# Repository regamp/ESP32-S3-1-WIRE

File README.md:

ESP32_S3 Waveshare IO and 1-wire

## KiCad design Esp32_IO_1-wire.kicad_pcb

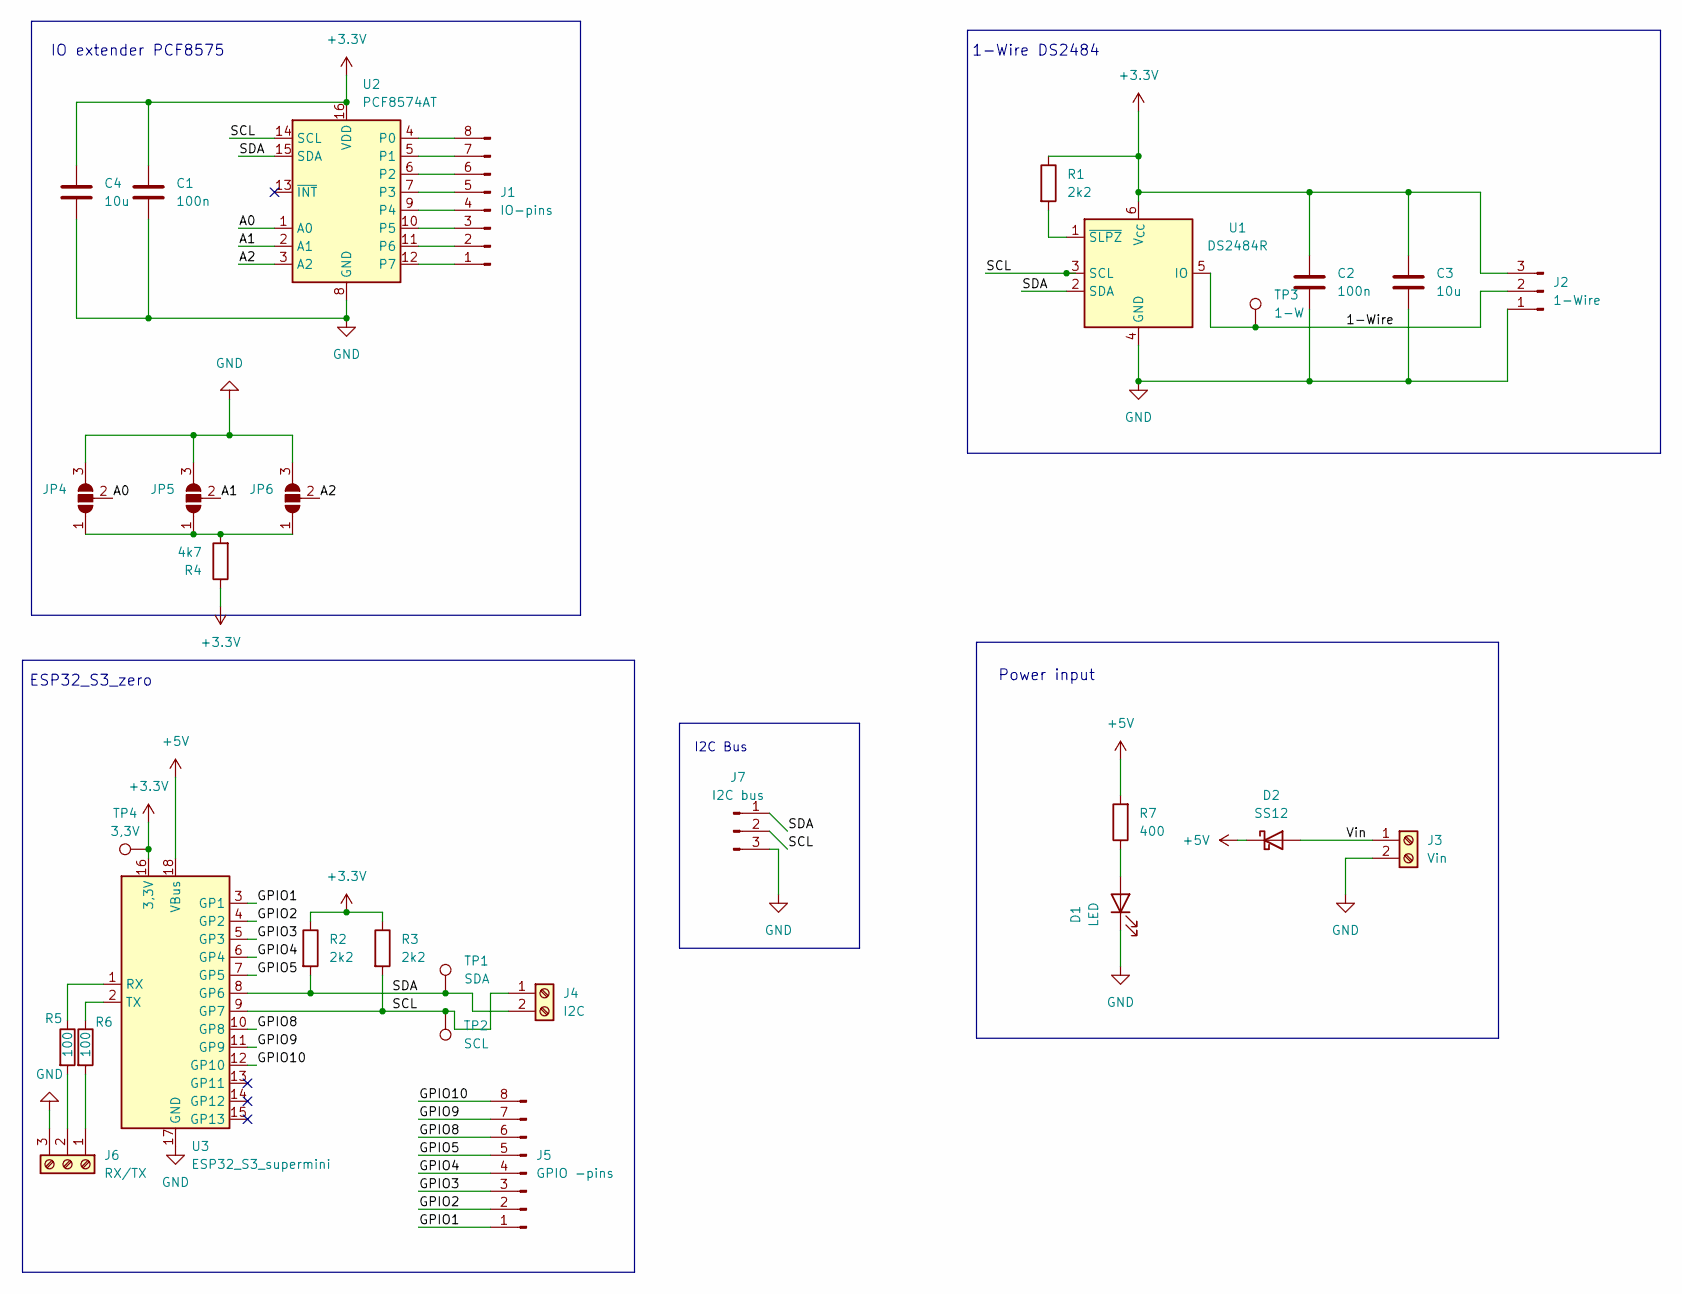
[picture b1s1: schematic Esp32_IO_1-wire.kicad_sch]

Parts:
C1, C2: 100n; C_0805_2012Metric_Pad1.18x1.45mm_HandSolder
C3, C4: 10u; C_0805_2012Metric_Pad1.18x1.45mm_HandSolder
D1: LED; LED_0805_2012Metric_Pad1.15x1.40mm_HandSolder
D2: SS12; D_SMA_Handsoldering
J1: IO-pins; PinSocket_1x08_P2.54mm_Vertical
J2: 1-Wire; TerminalBlock_4Ucon_1x03_P3.50mm_Horizontal
J3: Vin; TerminalBlock_MetzConnect_Type059_RT06302HBWC_1x02_P3.50mm_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
J4: I2C; TerminalBlock_MetzConnect_Type059_RT06302HBWC_1x02_P3.50mm_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
J5: GPIO -pins; PinSocket_1x08_P2.54mm_Vertical
J6: RX/TX; TerminalBlock_Phoenix_PT-1,5-3-3.5-H_1x03_P3.50mm_Horizontal
J7: I2C bus; PinHeader_1x03_P1.27mm_Horizontal
JP4, JP5, JP6: SolderJumper_3_Open; SolderJumper-3_P1.3mm_Open_RoundedPad1.0x1.5mm_NumberLabels
R1, R2, R3: 2k2; R_0805_2012Metric_Pad1.20x1.40mm_HandSolder
R4: 4k7; R_0805_2012Metric_Pad1.20x1.40mm_HandSolder
R5, R6: 100; R_0805_2012Metric_Pad1.20x1.40mm_HandSolder
R7: 400; R_0805_2012Metric_Pad1.20x1.40mm_HandSolder
TP1: SDA; TestPoint_Pad_D1.0mm
TP2: SCL; TestPoint_Pad_D1.0mm
TP3: 1-W; TestPoint_Pad_D1.0mm
TP4: 3,3V; TestPoint_Pad_D1.0mm
U1: DS2484R; SOT-23-6_Handsoldering
U2: PCF8574AT; SOIC-16W_7.5x10.3mm_P1.27mm
U3: ESP32_S3_supermini

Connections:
+3.3V: C1.1, C2.1, C3.1, C4.1, J2.3, R1.1, R2.1, R3.1, R4.1, TP4.1 (1_1), U1.6 (V_{CC}), U2.16 (VDD), U3.16 (3,3V)
+5V: D2.1 (K), R7.2, U3.18 (VBus)
/1-Wire: J2.2, TP3.1, U1.5 (IO)
/A0: JP4.2 (C), U2.1 (A0)
/A1: JP5.2 (C), U2.2 (A1)
/A2: JP6.2 (C), U2.3 (A2)
/GPIO1: J5.1, U3.3 (GP1)
/GPIO2: J5.2, U3.4 (GP2)
/GPIO3: J5.3, U3.5 (GP3)
/GPIO4: J5.4, U3.6 (GP4)
/GPIO5: J5.5, U3.7 (GP5)
/GPIO8: J5.6, U3.10 (GP8)
/GPIO9: J5.7, U3.11 (GP9)
/GPIO10: J5.8, U3.12 (GP10)
/SCL: J4.1, J7.2, R3.2, TP2.1 (1_1), U1.3 (SCL), U2.14 (SCL), U3.9 (GP7)
/SDA: J4.2, J7.1, R2.2, TP1.1 (1_1), U1.2 (SDA), U2.15 (SDA), U3.8 (GP6)
/Vin: D2.2 (A), J3.1
GND: C1.2, C2.2, C3.2, C4.2, D1.1 (K), J2.1, J3.2, J6.3, J7.3, JP4.3 (B), JP5.3 (B), JP6.3 (B), U1.4 (GND), U2.8 (GND), U3.17 (GND)
unnamed: D1.2 (A), R7.1
unnamed: J1.1, U2.12 (P7)
unnamed: J1.2, U2.11 (P6)
unnamed: J1.3, U2.10 (P5)
unnamed: J1.4, U2.9 (P4)
unnamed: J1.5, U2.7 (P3)
unnamed: J1.6, U2.6 (P2)
unnamed: J1.7, U2.5 (P1)
unnamed: J1.8, U2.4 (P0)
unnamed: J6.1, R6.2
unnamed: J6.2, R5.2
unnamed: JP4.1 (A), JP5.1 (A), JP6.1 (A), R4.2
unnamed: R1.2, U1.1 (~SLPZ)
unnamed: R5.1, U3.1 (RX)
unnamed: R6.1, U3.2 (TX)

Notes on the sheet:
Power input
1-Wire DS2484
I2C Bus
IO extender PCF8575
ESP32_S3_zero

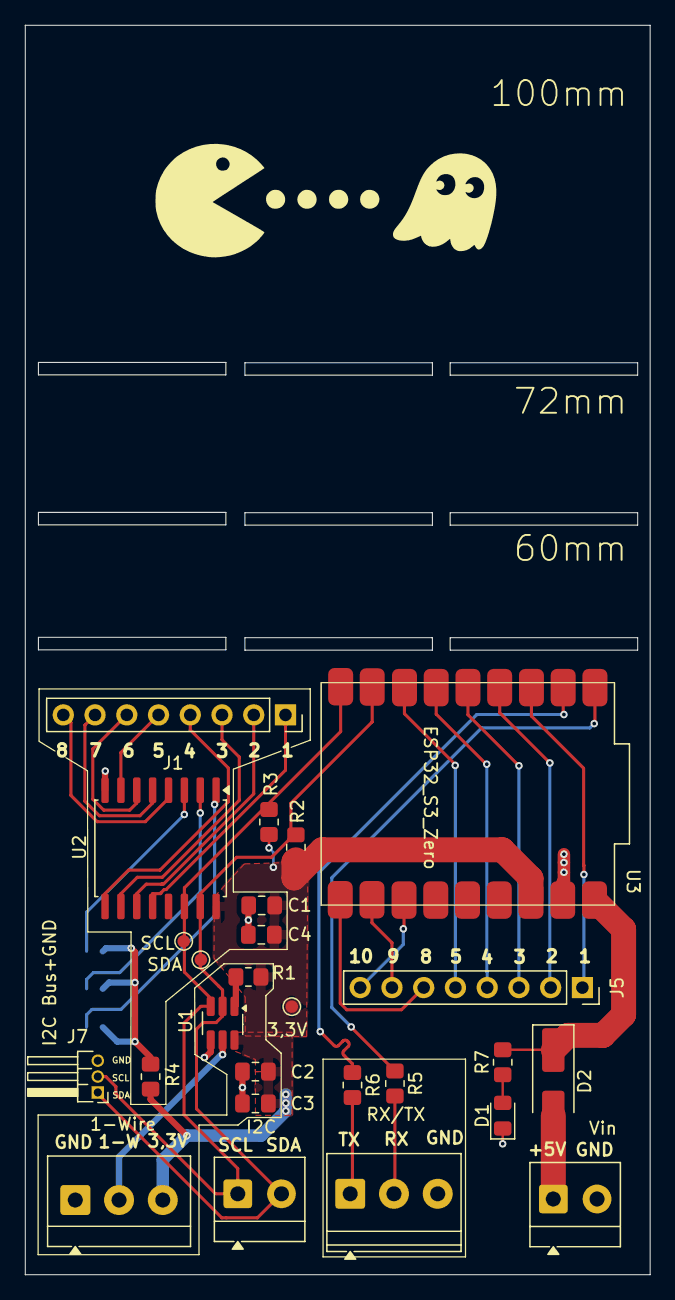
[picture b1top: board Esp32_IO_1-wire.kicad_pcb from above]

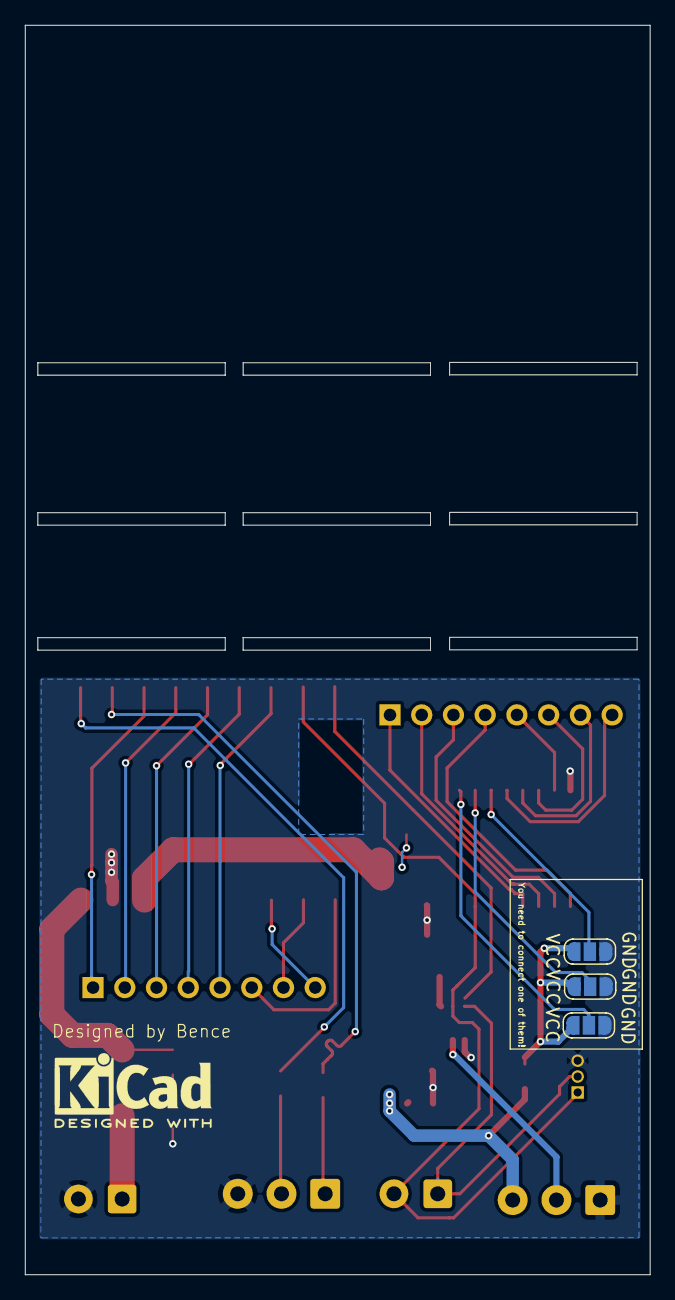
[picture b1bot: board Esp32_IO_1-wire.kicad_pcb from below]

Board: 2 copper layers, 50.0 x 100.0 mm, 29 parts (3 on the bottom side), 33 nets.

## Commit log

2026-04-23 I2C Bus with 1,27mm pinheader
2026-04-23 Picture
2026-04-24 I2C routing fix
2026-04-24 Logo
2026-04-25 pacman
